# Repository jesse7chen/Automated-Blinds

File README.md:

# Automated-Blinds

Code and supporting material to create a product which can open/close blinds based on a user's predefined input times or at command. Product consists of both a receiver and transmitter which communicate over IR.

The microcontroller used was a LPC1114fn28/102, which interfaced to a 128x32 OLED screen via I2C. The screen's driver is the SSD1306.

See demo video here!

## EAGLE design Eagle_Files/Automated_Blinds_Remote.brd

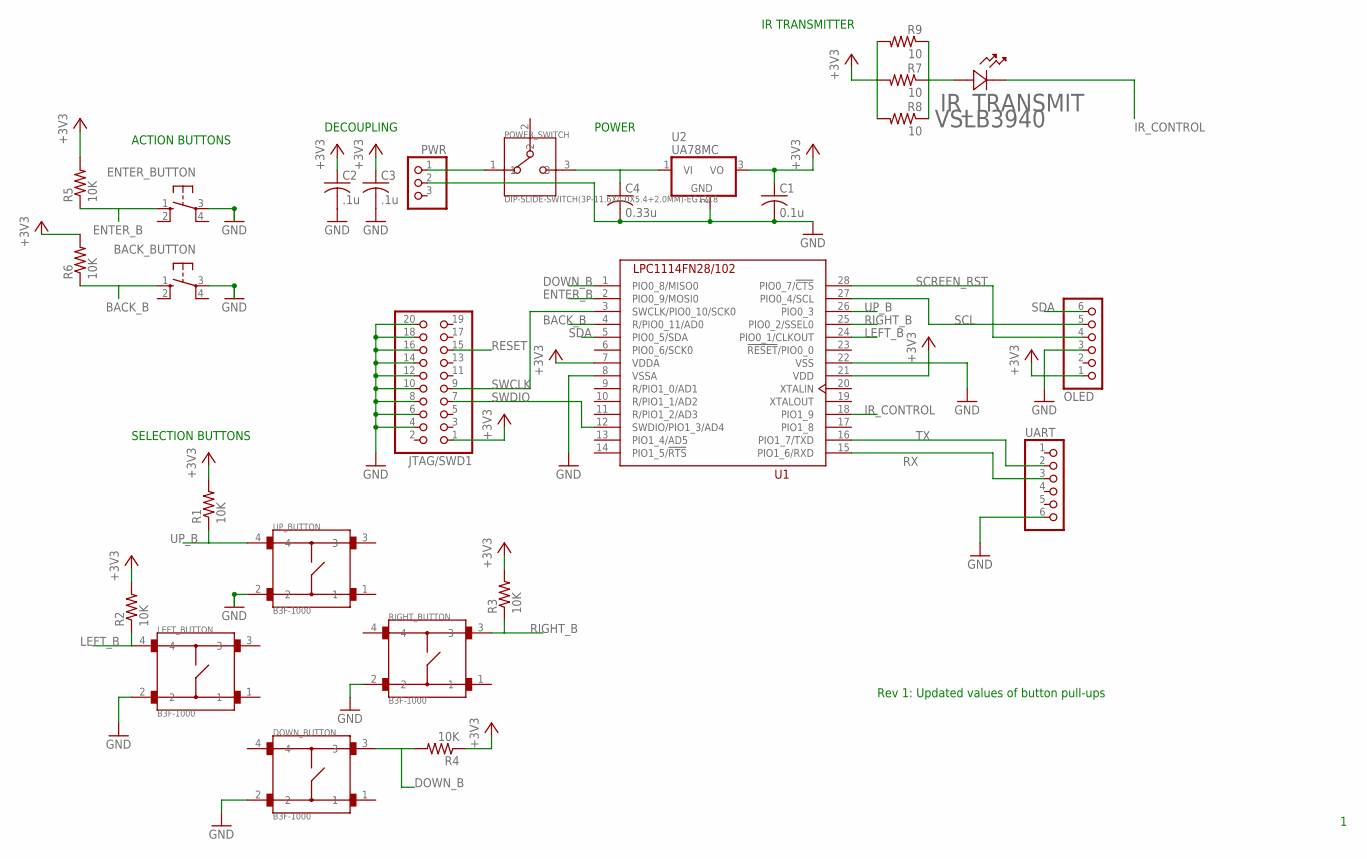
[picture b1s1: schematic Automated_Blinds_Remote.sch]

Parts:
BACK_BUTTON: 40/XX; B3F/40XX
C1: 0.1u; C050-024X044
C2, C3: .1u; C050-024X044
C4: 0.33u; C050-024X044
DOWN_BUTTON: B3F-1000; SW_B3F-1000
ENTER_BUTTON: 40/XX; B3F/40XX
IR_TRANSMIT: VSLB3940; LED_TLH
JTAG/SWD1: PINHD-2X10; 2X10
LEFT_BUTTON: B3F-1000; SW_B3F-1000
OLED: PINHD-1X6; 1X06
POWER_SWITCH: DIP-SLIDE-SWITCH(3P-11.6X4.0X5.4+2.0MM)-EG1218; SW3-2.5-11.6X4.0X5.4+2.0MM
PWR: PINHD-1X3; 1X03
R1, R2, R3, R4, R5, R6: 10K; 0207/10
R7, R8, R9: 10; 0207/10
RIGHT_BUTTON: B3F-1000; SW_B3F-1000
U1: LPC1114FN28/102; DIL28-6
U2: UA78MC; TO220V
UART: PINHD-1X6; 1X06
UP_BUTTON: B3F-1000; SW_B3F-1000

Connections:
+3V3: C1.1, C2.1, C3.1, JTAG/SWD1.1, OLED.1, R1.2, R2.2, R3.2, R4.1, R5.2, R6.2, R7.2, R8.2, R9.2, U1.7 (VDDA), U1.21 (VDD), U2.3 (VO)
BACK_B: BACK_BUTTON.1 (S), R6.1, U1.4 (R/PIO0_11/AD0)
DOWN_B: DOWN_BUTTON.3, R4.2, U1.1 (PIO0_8/MISO0)
ENTER_B: ENTER_BUTTON.1 (S), R5.1, U1.2 (PIO0_9/MOSI0)
GND: BACK_BUTTON.3, C1.2, C2.2, C3.2, C4.2, DOWN_BUTTON.2, ENTER_BUTTON.3, JTAG/SWD1.4, JTAG/SWD1.6, JTAG/SWD1.8, JTAG/SWD1.10, JTAG/SWD1.12, JTAG/SWD1.14, JTAG/SWD1.16, JTAG/SWD1.18, JTAG/SWD1.20, LEFT_BUTTON.2, OLED.3, PWR.2, RIGHT_BUTTON.2, U1.8 (VSSA), U1.22 (VSS), U2.2 (GND), UART.6, UP_BUTTON.2
IR_CONTROL: IR_TRANSMIT.1 (11), U1.18 (PIO1_9)
LEFT_B: LEFT_BUTTON.4, R2.1, U1.24 (PIO0_1/CLKOUT)
unnamed: IR_TRANSMIT.2 (22), R7.1, R8.1, R9.1
unnamed: POWER_SWITCH.1, PWR.1
unnamed: C4.1, POWER_SWITCH.3, U2.1 (VI)
RESET: JTAG/SWD1.15
RIGHT_B: R3.1, RIGHT_BUTTON.3, U1.25 (PIO0_2/SSEL0)
RX: U1.15 (PIO1_6/RXD), UART.3
SCL: OLED.5, U1.27 (PIO0_4/SCL)
SCREEN_RST: OLED.4, U1.28 (PIO0_7/!CTS)
SDA: OLED.6, U1.5 (PIO0_5/SDA)
SWCLK: JTAG/SWD1.9, U1.3 (SWCLK/PIO0_10/SCK0)
SWDIO: JTAG/SWD1.7, U1.12 (SWDIO/PIO1_3/AD4)
TX: U1.16 (PIO1_7/TXD), UART.2
UP_B: R1.1, U1.26 (PIO0_3), UP_BUTTON.4

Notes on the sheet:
POWER
DECOUPLING
ACTION BUTTONS
SELECTION BUTTONS
IR TRANSMITTER
Rev 1: Updated values of button pull-ups

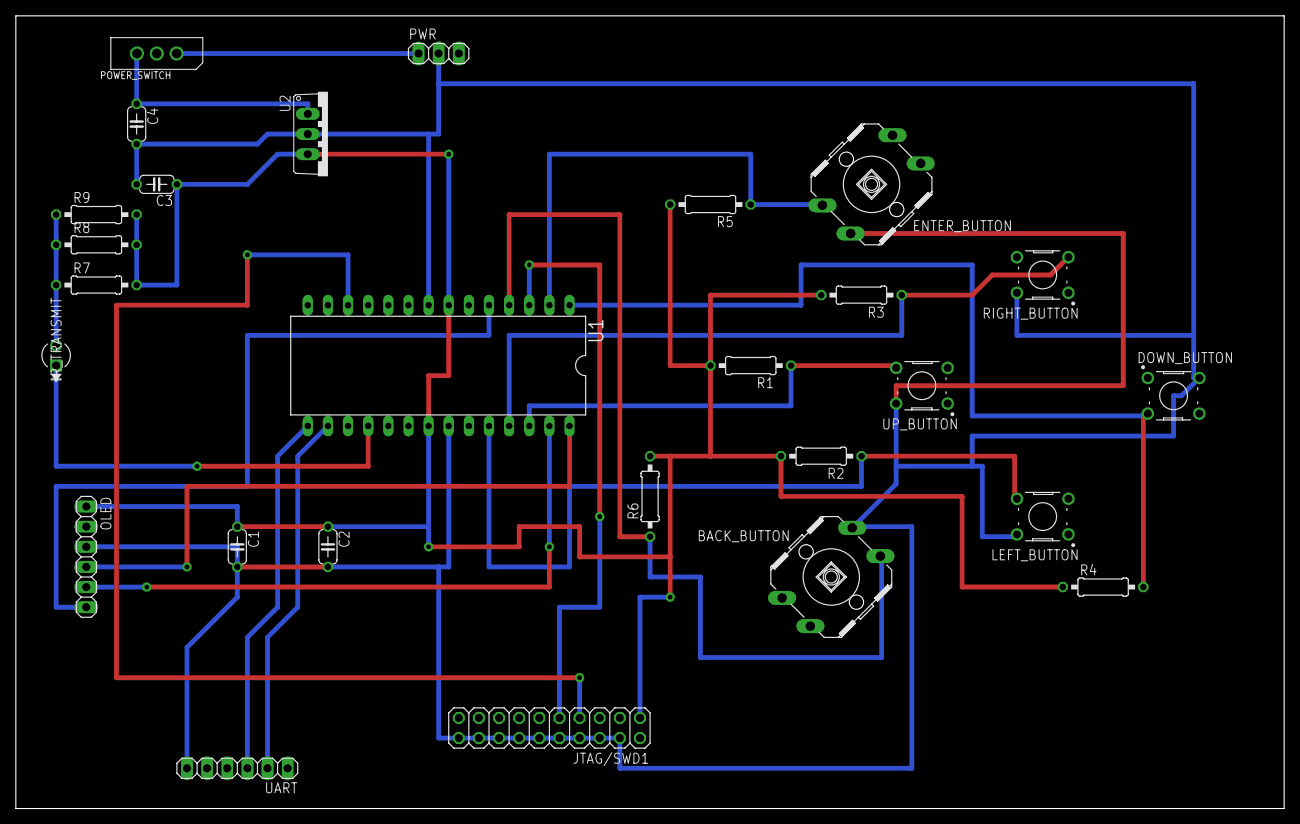
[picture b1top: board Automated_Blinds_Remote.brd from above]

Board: 2 copper layers, 160.0 x 100.0 mm, 27 parts (0 on the bottom side), 19 nets.

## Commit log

2017-10-01 Added initial files - Rough I2C implemented
2017-10-02 Wrote screen_init and screen_display functions
2017-10-04 Font library, string drawing functionality
    Wrote pixel drawing and char drawing functions to implement string drawing function
2017-10-04 Can now invert character colors
2017-10-07 Fixed char spacing, started UI functions
2017-10-08 Implemented ability to display and change times
2017-10-20 Began button reading drivers
2017-11-11 Added timer based interrupt, seemingly does not work
2017-11-14 Completed button debouncing code and linked with UI
2017-11-15 Interrupt-based button polling and button presses
2017-11-16 UI now interfaced with buttons
2017-11-19 Finished UI, began IR transmission drivers
2017-11-19 Finished IR transmission driver
2017-12-04 Started PCB design
2017-12-06 Finished PCB design for remote control
2017-12-09 Updated value of button pull-ups in schematic
2017-12-09 Fixed IR match timer value for 1kHz
